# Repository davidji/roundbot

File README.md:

This is a 3D printable robot with MBED control software. It uses signal processing to reduce the component count normally associated with quadrature encoding.

There are also lots of other objects defined in [Solid Python](https://github.com/SolidCode/SolidPython) loosely associated with the project

The build and all the dependencies for the software come from [PlatformIO](http://platformio.org/).

The 3D models require [Solid Python](https://github.com/SolidCode/SolidPython) and [OpenSCAD](http://www.openscad.org/)

TODO: The hardware needs some explanation

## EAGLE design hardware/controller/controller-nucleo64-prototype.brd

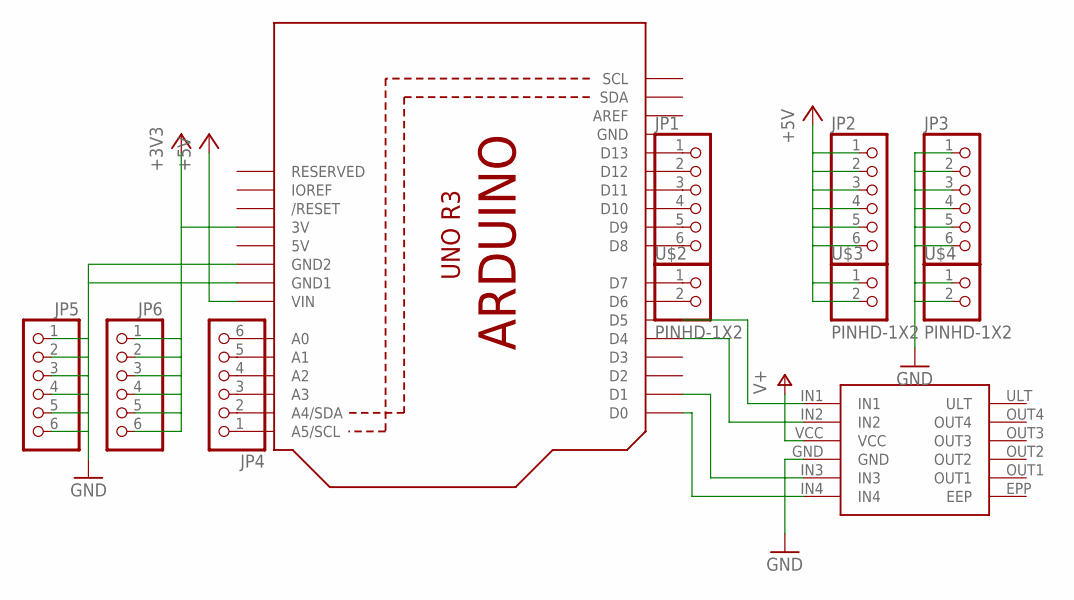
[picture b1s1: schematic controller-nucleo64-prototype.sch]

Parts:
JP1, JP2, JP3, JP4, JP5, JP6: PINHD-1X6CB; 1X06-CLEANBIG
U1: ARDUINOR3-DIMENSION; ARDUINOR3
U$1: DRV8833-MODULEUPSIDE-DOWN; DRV8833-BRKOUT-INV
U$2, U$3, U$4: PINHD-1X2; 1X02-CLEANBIG

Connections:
5V: U1.5V
+3V3: JP6.1, JP6.2, JP6.3, JP6.4, JP6.5, JP6.6, U1.3V
+5V: JP2.1, JP2.2, JP2.3, JP2.4, JP2.5, JP2.6, U1.VIN, U$3.1, U$3.2
GND: JP3.1, JP3.2, JP3.3, JP3.4, JP3.5, JP3.6, JP5.1, JP5.2, JP5.3, JP5.4, JP5.5, JP5.6, U1.GND, U1.GND1, U1.GND2, U$1.GND, U$4.1, U$4.2
unnamed: U1.D0, U$1.IN4
unnamed: U1.D1, U$1.IN3
unnamed: U1.D4, U$1.IN2
unnamed: U1.D5, U$1.IN1
unnamed: JP1.1, U1.D13
unnamed: JP1.2, U1.D12
unnamed: JP1.3, U1.D11
unnamed: JP1.4, U1.D10
unnamed: JP1.5, U1.D9
unnamed: JP1.6, U1.D8
unnamed: JP4.1, U1.A5 (A5/SCL)
unnamed: JP4.2, U1.A4 (A4/SDA)
unnamed: JP4.3, U1.A3
unnamed: JP4.4, U1.A2
unnamed: JP4.5, U1.A1
unnamed: JP4.6, U1.A0
unnamed: U1.D7, U$2.1
unnamed: U1.D6, U$2.2
V+: U$1.VCC

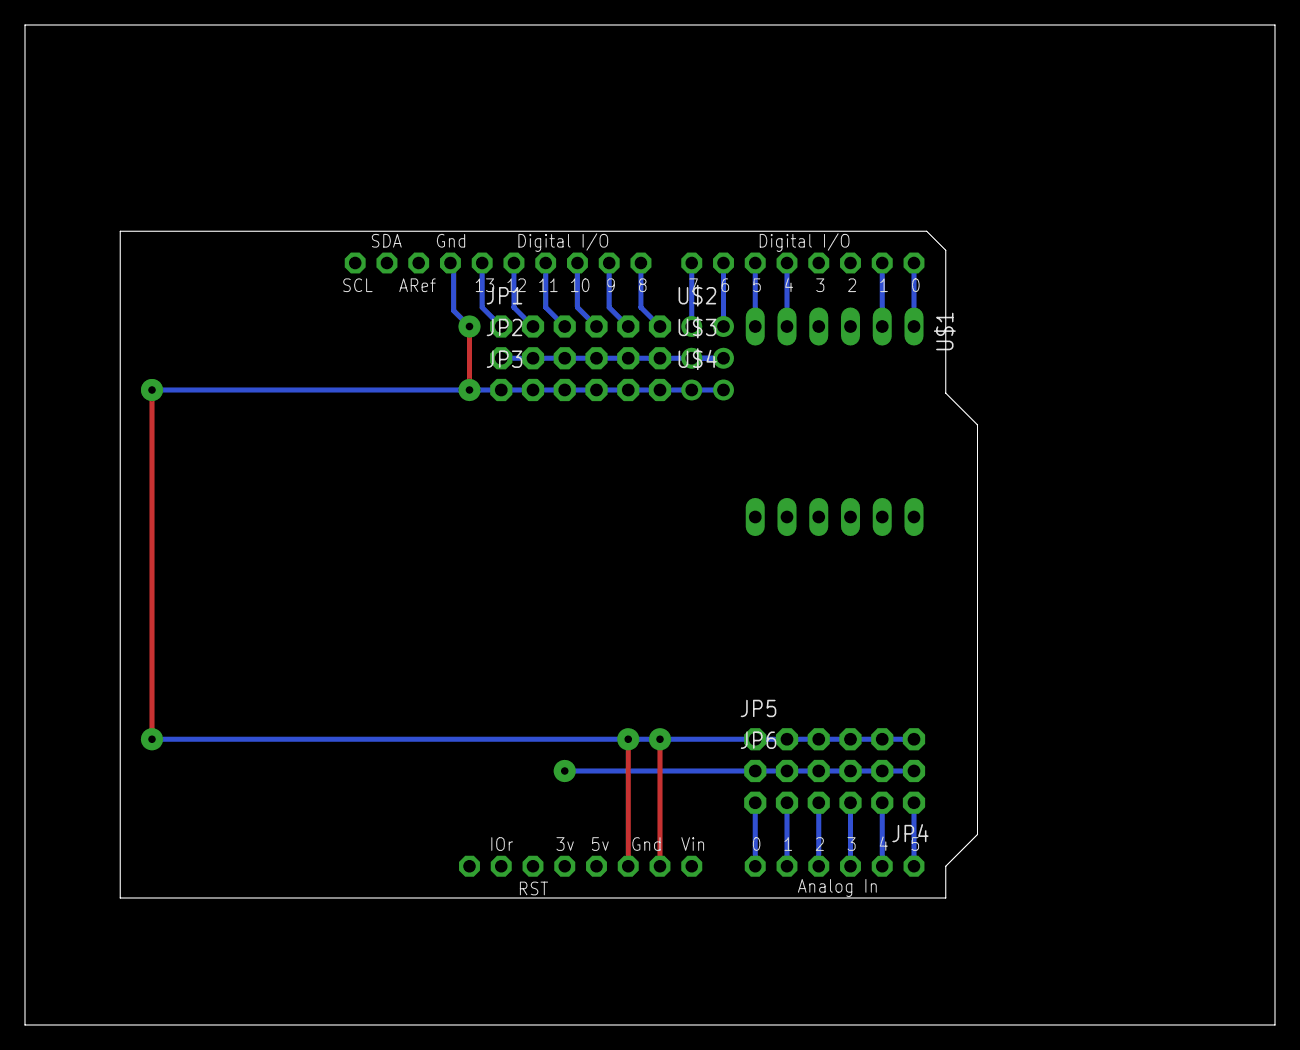
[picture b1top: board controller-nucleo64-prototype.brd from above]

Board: 2 copper layers, 100.0 x 80.0 mm, 11 parts (0 on the bottom side), 21 nets.

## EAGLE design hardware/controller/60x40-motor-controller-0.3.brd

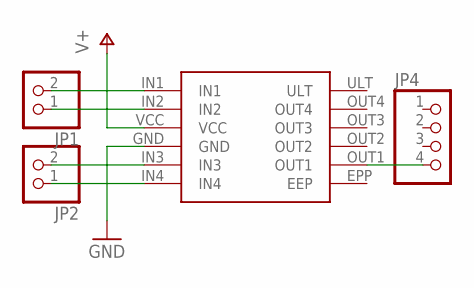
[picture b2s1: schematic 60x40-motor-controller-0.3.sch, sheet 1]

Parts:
JP1, JP2: PINHD-1X2/90; 1X02/90
JP4: PINHD-1X4/90; 1X04/90
U$1: DRV8833-MODULE; DRV8833-BRKOUT

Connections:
GND: U$1.GND; also elsewhere on the board
unnamed: JP2.2, U$1.IN3
unnamed: JP2.1, U$1.IN4
unnamed: JP1.2, U$1.IN1
unnamed: JP1.1, U$1.IN2
unnamed: JP4.4, U$1.OUT1
V+: U$1.VCC; also elsewhere on the board

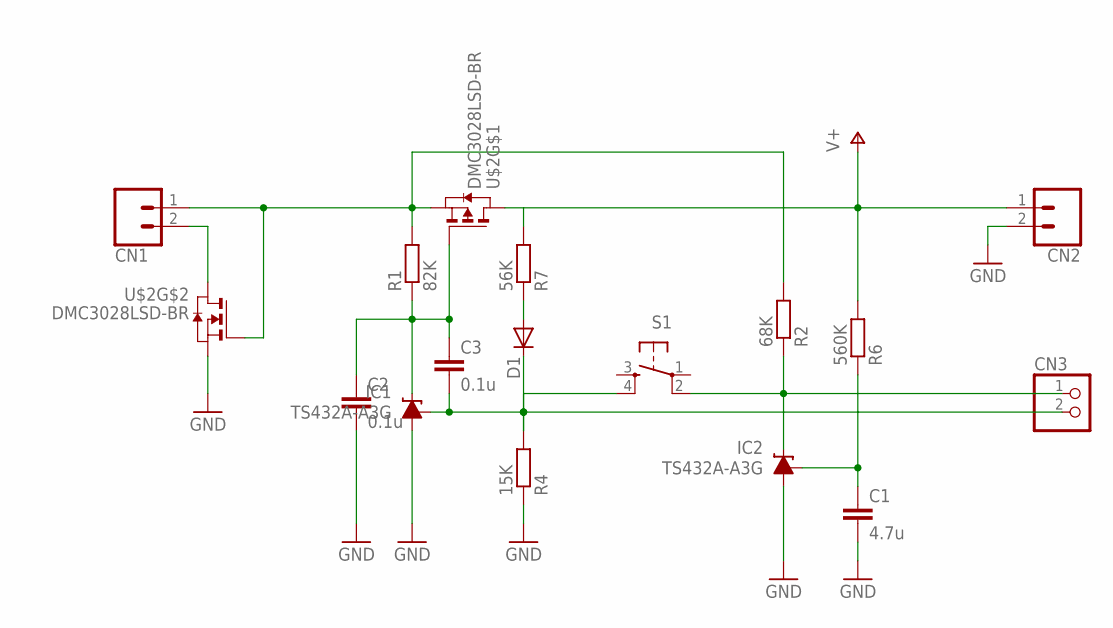
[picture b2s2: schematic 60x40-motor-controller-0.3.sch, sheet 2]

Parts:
C1: 4.7u; C025-025X050
C2, C3: 0.1u; C025-024X044
CN1, CN2: CONN_02-JST-XTH; JST-2-XTH
CN3: PINHD-1X2/90; 1X02/90
D1: DIODE-D-5; D-5
IC1, IC2: TS432A-A3G; TO92-LINE
R1: 82K; 0204V
R2: 68K; 0204/7
R4: 15K; 0204V
R6: 560K; 0207/10
R7: 56K; 0204V
S1: PROTO-MICRO-SWITCH; B3F-10XX-PROTO
U$2: DMC3028LSD-BR; DIL8-BREAKOUT

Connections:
GND: C1.2, C2.2, CN2.2, IC1.2 (A), IC2.2 (A), R4.1, U$2.1 (S); also elsewhere on the board
unnamed: CN1.1, R1.2, R2.2, U$2.2 (G), U$2.3 (S)
unnamed: C2.1, C3.1, IC1.1 (C), R1.1, U$2.4 (G)
unnamed: CN1.2, U$2.7 (D), U$2.8 (D)
unnamed: C3.2, CN3.2, D1.C, IC1.3 (FB), R4.2, S1.4 (S1)
unnamed: CN3.1, IC2.1 (C), R2.1, S1.2 (P1)
unnamed: C1.1, IC2.3 (FB), R6.1
unnamed: D1.A, R7.1
V+: CN2.1, R6.2, R7.2, U$2.5 (D), U$2.6 (D); also elsewhere on the board

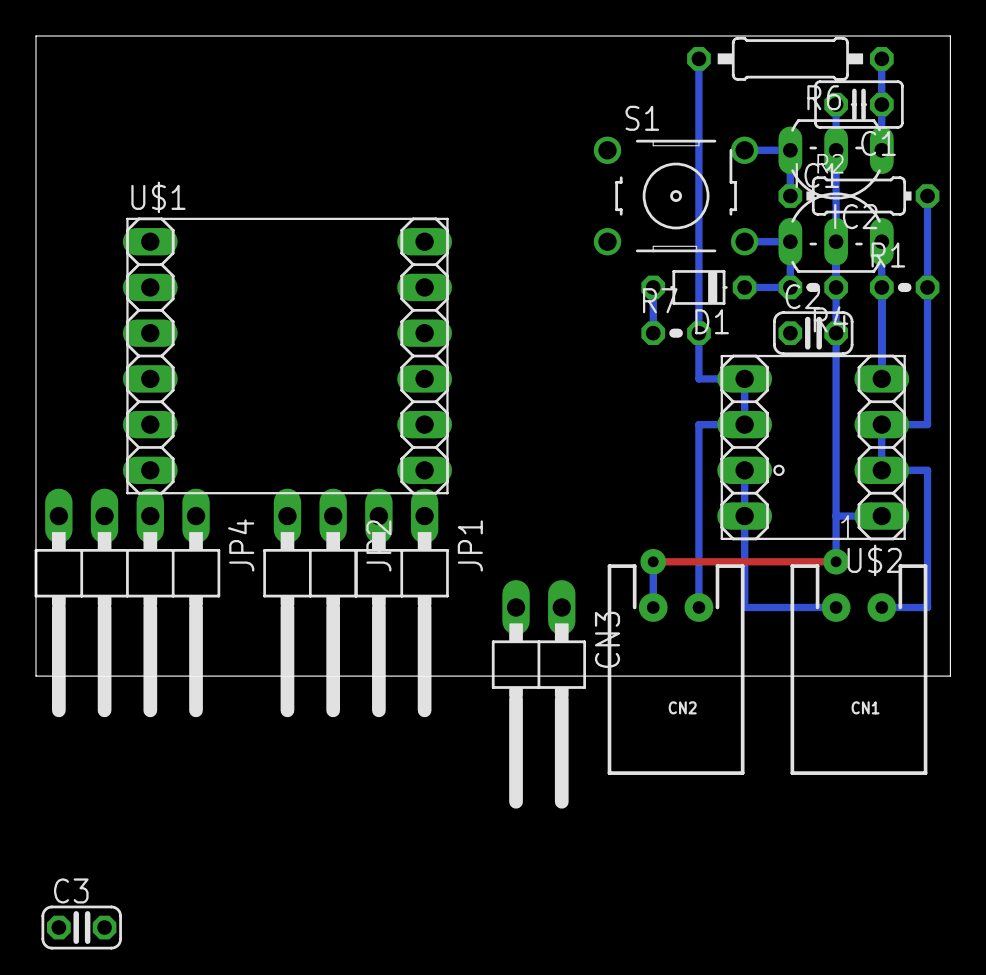
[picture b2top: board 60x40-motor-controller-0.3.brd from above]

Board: 2 copper layers, 50.8 x 35.6 mm, 20 parts (0 on the bottom side), 14 nets.

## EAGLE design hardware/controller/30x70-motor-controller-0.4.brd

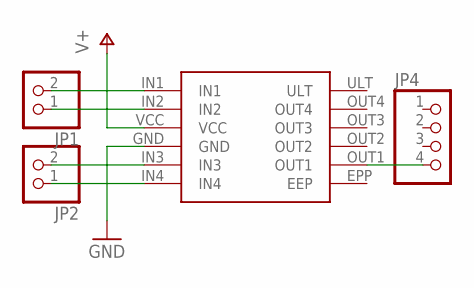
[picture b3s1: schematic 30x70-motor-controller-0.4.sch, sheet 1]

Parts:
JP1, JP2: PINHD-1X2/90; 1X02/90
JP4: PINHD-1X4/90; 1X04/90
U$1: DRV8833-MODULE; DRV8833-BRKOUT

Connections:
GND: U$1.GND; also elsewhere on the board
unnamed: JP2.2, U$1.IN3
unnamed: JP2.1, U$1.IN4
unnamed: JP1.2, U$1.IN1
unnamed: JP1.1, U$1.IN2
unnamed: JP4.4, U$1.OUT1
V+: U$1.VCC; also elsewhere on the board

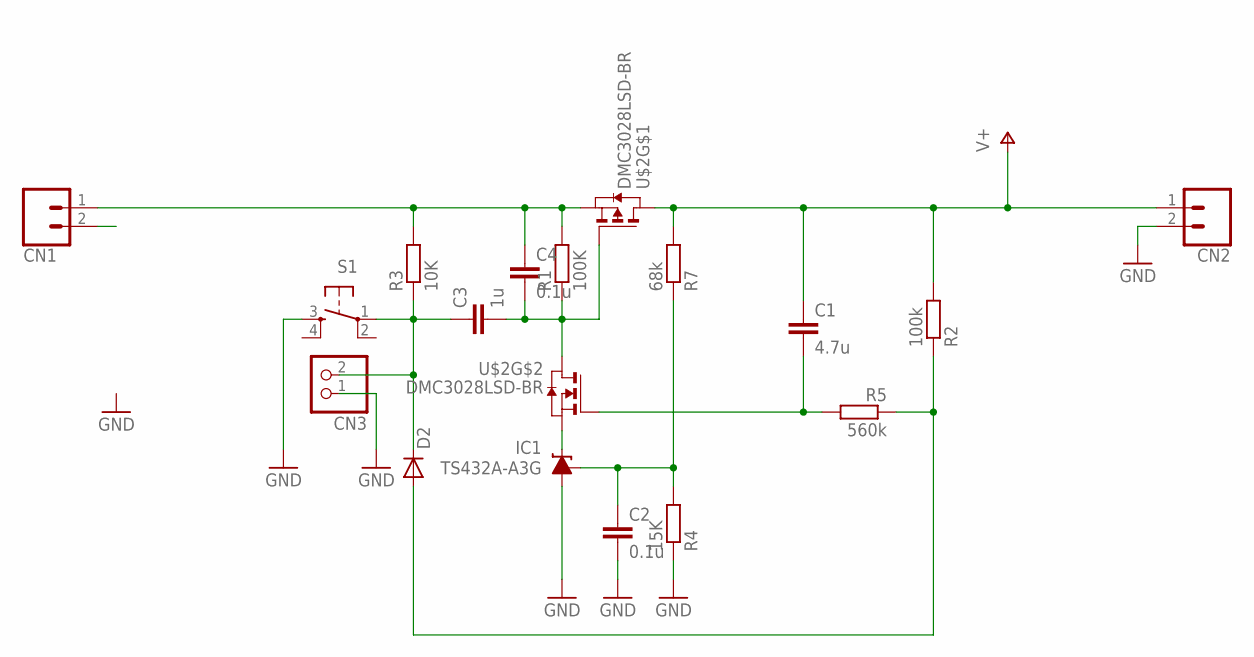
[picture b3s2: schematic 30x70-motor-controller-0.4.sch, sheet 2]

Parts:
C1: 4.7u; C025-025X050
C2, C4: 0.1u; C025-024X044
C3: 1u; C025-024X044
CN1, CN2: CONN_02-JST-XTH; JST-2-XTH
CN3: PINHD-1X2/90; 1X02/90
D2: DIODE-D-2.5; D-2.5
IC1: TS432A-A3G; TO92-LINE
R1: 100K; 0204V
R2: 100k; 0204V
R3: 10K; 0204V
R4: 15K; 0204V
R5: 560k; 0204/7
R7: 68k; 0204/7
S1: PROTO-MICRO-SWITCH; B3F-10XX-PROTO
U$2: DMC3028LSD-BR; DIL8-BREAKOUT

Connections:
GND: C2.2, CN2.2, CN3.1, IC1.2 (A), R4.1, S1.3 (S); also elsewhere on the board
unnamed: C4.1, CN1.1, R1.2, R3.2, U$2.3 (S)
unnamed: C3.2, C4.2, R1.1, U$2.4 (G), U$2.7 (D), U$2.8 (D)
unnamed: C2.1, IC1.3 (FB), R4.2, R7.1
unnamed: C1.2, R5.2, U$2.2 (G)
unnamed: D2.A, R2.1, R5.1
unnamed: IC1.1 (C), U$2.1 (S)
unnamed: C3.1, CN3.2, D2.C, R3.1, S1.1
V+: C1.1, CN2.1, R2.2, R7.2, U$2.5 (D), U$2.6 (D); also elsewhere on the board

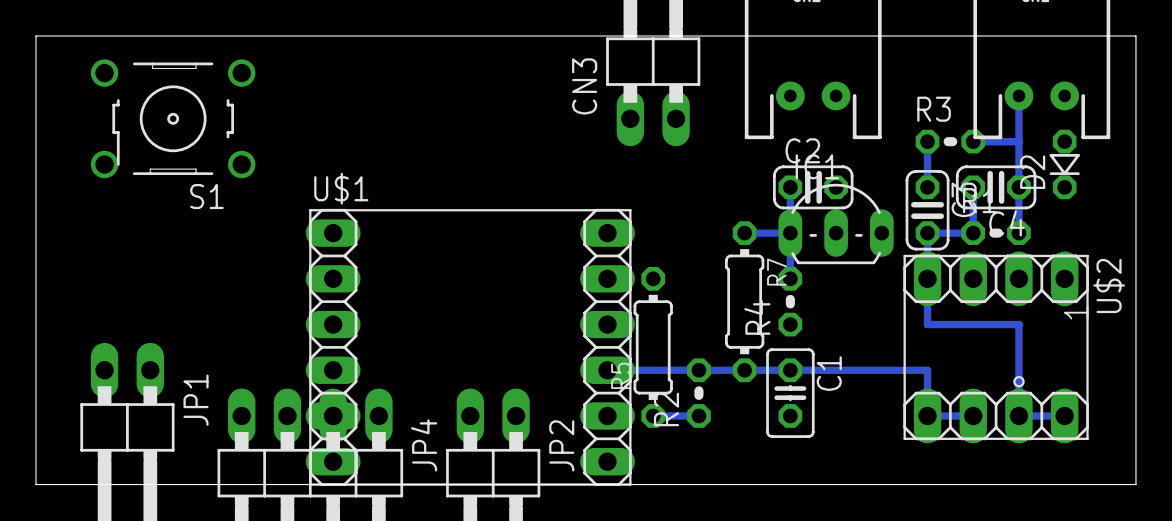
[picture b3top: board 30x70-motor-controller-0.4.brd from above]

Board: 2 copper layers, 61.1 x 24.9 mm, 21 parts (0 on the bottom side), 14 nets.

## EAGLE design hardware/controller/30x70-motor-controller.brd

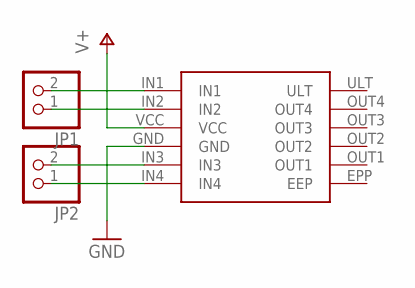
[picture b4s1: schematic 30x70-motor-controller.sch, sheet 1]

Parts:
JP1, JP2: PINHD-1X2/90; 1X02/90
U$1: DRV8833-MODULE; DRV8833-BRKOUT

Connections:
GND: U$1.GND; also elsewhere on the board
unnamed: JP2.2, U$1.IN3
unnamed: JP2.1, U$1.IN4
unnamed: JP1.2, U$1.IN1
unnamed: JP1.1, U$1.IN2
V+: U$1.VCC; also elsewhere on the board

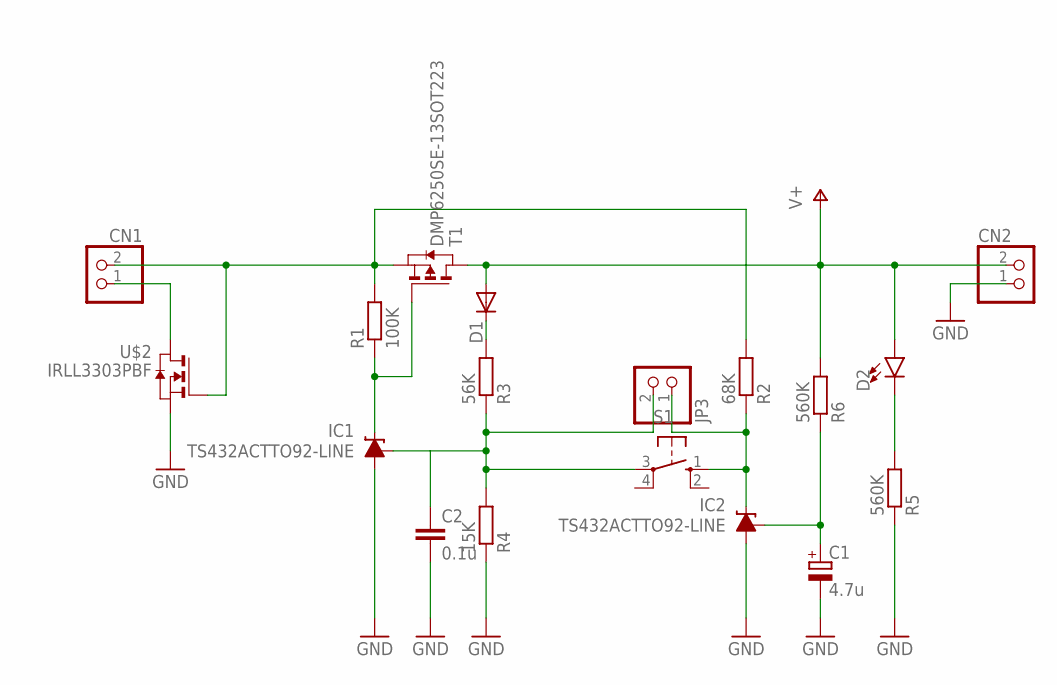
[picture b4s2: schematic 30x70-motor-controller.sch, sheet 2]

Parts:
C1: 4.7u; E2,5-5
C2: 0.1u; C025-024X044
CN1, CN2: JST_2PIN-THM-RA; JST-PH-2-THM-RA
D1: DIODE-D-2.5; D-2.5
D2: LED-3MM-NO_SILK; LED_3MM-NS
IC1, IC2: TS432ACTTO92-LINE; TO92-LINE
JP3: PINHD-1X2/90; 1X02/90
R1: 100K; 0204/5
R2: 68K; 0204/5
R3: 56K; 0204/5
R4: 15K; 0204V
R5, R6: 560K; 0204/5
S1: 10-XX; B3F-10XX
T1: DMP6250SE-13SOT223; SOT223
U$2: IRLL3303PBF; SOT223

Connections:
GND: C1.-, C2.2, CN2.1 (2), IC1.2 (A), IC2.2 (A), R4.1, R5.1, U$2.3 (S); also elsewhere on the board
unnamed: CN1.2 (1), R1.2, R2.2, T1.3 (S), U$2.1 (G)
unnamed: IC1.1 (C), R1.1, T1.1 (G)
unnamed: CN1.1 (2), U$2.2 (D), U$2.4 (D)
unnamed: C2.1, IC1.3 (FB), JP3.2, R3.1, R4.2, S1.3
unnamed: IC2.1 (C), JP3.1, R2.1, S1.1 (S)
unnamed: C1.+, IC2.3 (FB), R6.1
unnamed: D1.C, R3.2
unnamed: D2.K (C), R5.2
V+: CN2.2 (1), D1.A, D2.A, R6.2, T1.2 (D), T1.4 (D); also elsewhere on the board

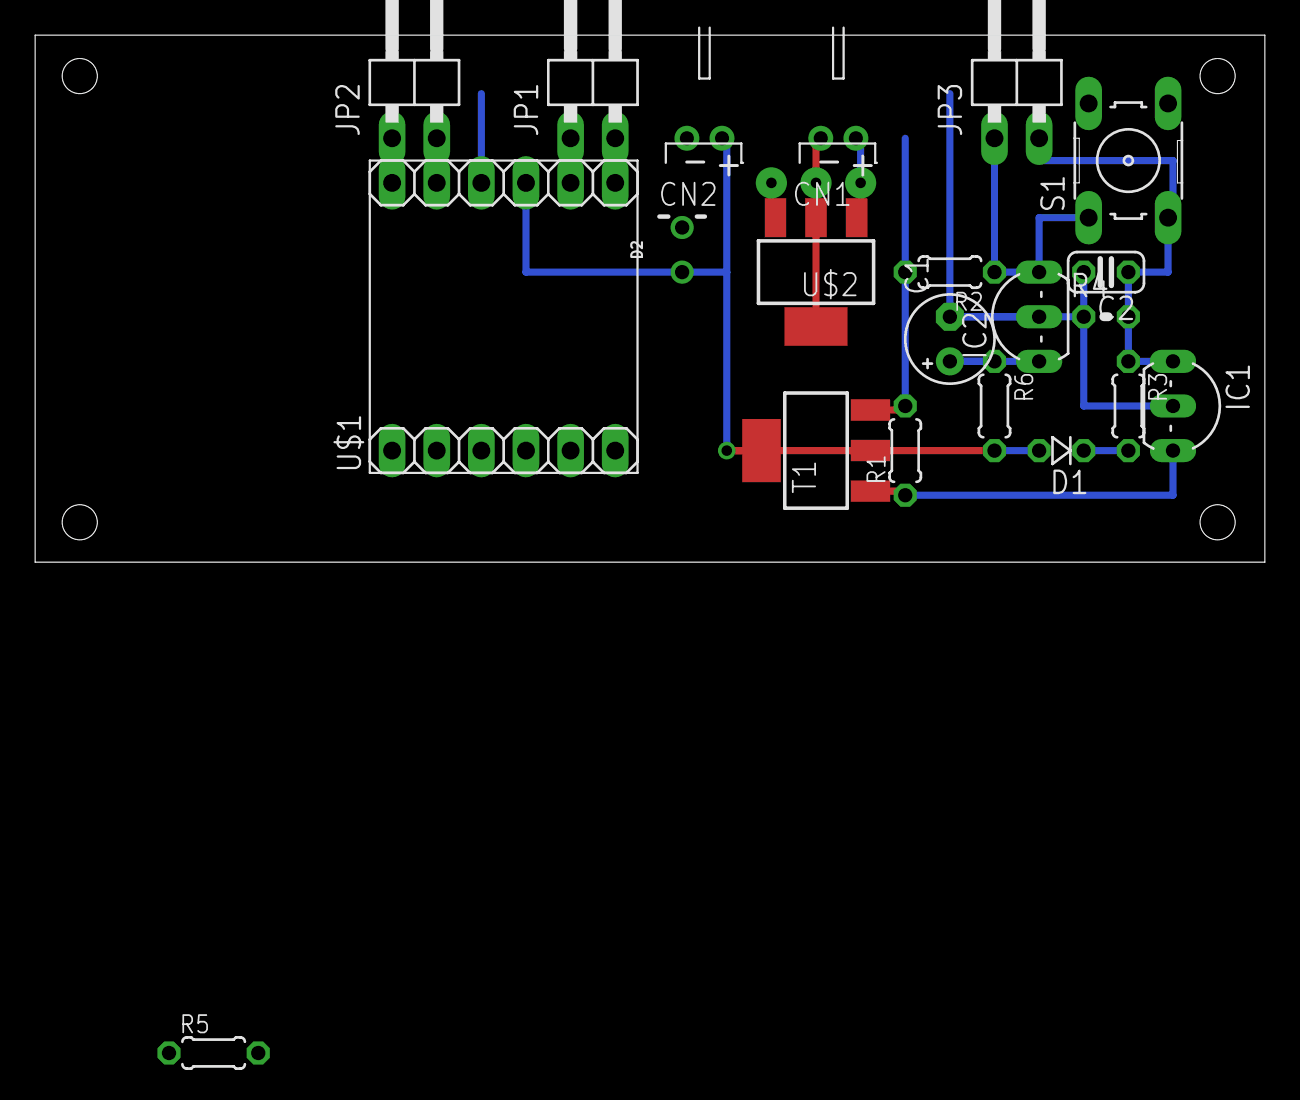
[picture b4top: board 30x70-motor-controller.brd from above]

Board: 2 copper layers, 70.0 x 30.0 mm, 21 parts (0 on the bottom side), 14 nets.

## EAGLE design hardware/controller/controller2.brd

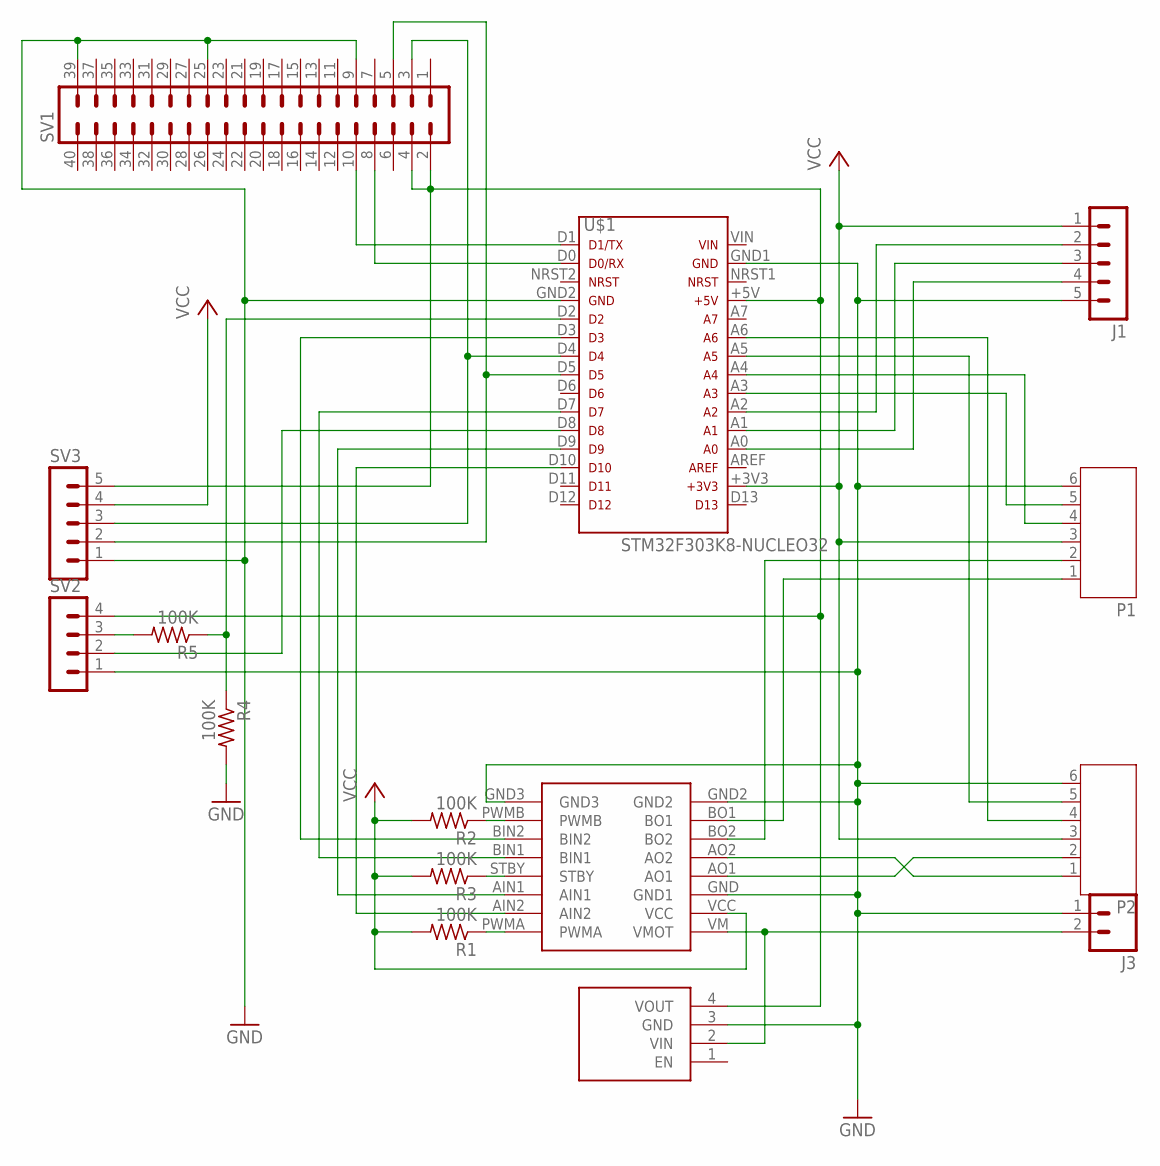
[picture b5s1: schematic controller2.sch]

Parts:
J1: MA05-1
J3: M02JST-PTH-VERT; JST-2-PTH-VERT
P1, P2: JST-PH6
R1, R2, R3, R4, R5: 100K; M0805
SV1: MA20-2
SV2: MA04-1
SV3: MA05-1
U$1: STM32F303K8-NUCLEO32; NUCLEO32
U$2: TB6612FNG-CARRIER/SPARKFUN; TB6612FNG-BRKOUT/SPARKFUN
U$3: S7V8A; S7V8

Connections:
GND: J1.5, J3.1, P1.6, P2.6, R4.2, SV1.9, SV1.25, SV1.39, SV2.1, SV3.1, U$1.GND1, U$1.GND2, U$2.GND (GND1), U$2.GND2, U$2.GND3, U$3.3 (GND)
unnamed: U$1.D3, U$2.BIN2
unnamed: U$1.D7, U$2.BIN1
unnamed: U$1.D9, U$2.AIN1
unnamed: U$1.D10, U$2.AIN2
unnamed: P2.2, U$2.AO1
unnamed: R2.1, U$2.PWMB
unnamed: R1.1, U$2.PWMA
unnamed: R3.1, U$2.STBY
unnamed: P2.1, U$2.AO2
unnamed: P1.2, U$2.BO2
unnamed: P1.1, U$2.BO1
unnamed: SV1.3, SV3.3, U$1.D4
unnamed: SV1.5, SV3.2, U$1.D5
unnamed: SV1.8, U$1.D0
unnamed: SV1.10, U$1.D1
unnamed: J3.2, U$2.VM (VMOT), U$3.2 (VIN)
unnamed: P1.4, U$1.A4
unnamed: P1.5, U$1.A3
unnamed: P2.4, U$1.A6
unnamed: P2.5, U$1.A5
unnamed: J1.2, U$1.A2
unnamed: J1.3, U$1.A1
unnamed: J1.4, U$1.A0
unnamed: R5.2, SV2.3
unnamed: SV1.2, SV1.4, SV2.4, SV3.5, U$1.+5V, U$3.4 (VOUT)
unnamed: R4.1, R5.1, U$1.D2
unnamed: SV2.2, U$1.D8
VCC: J1.1, P1.3, P2.3, R1.2, R2.2, R3.2, SV3.4, U$1.+3V3, U$2.VCC

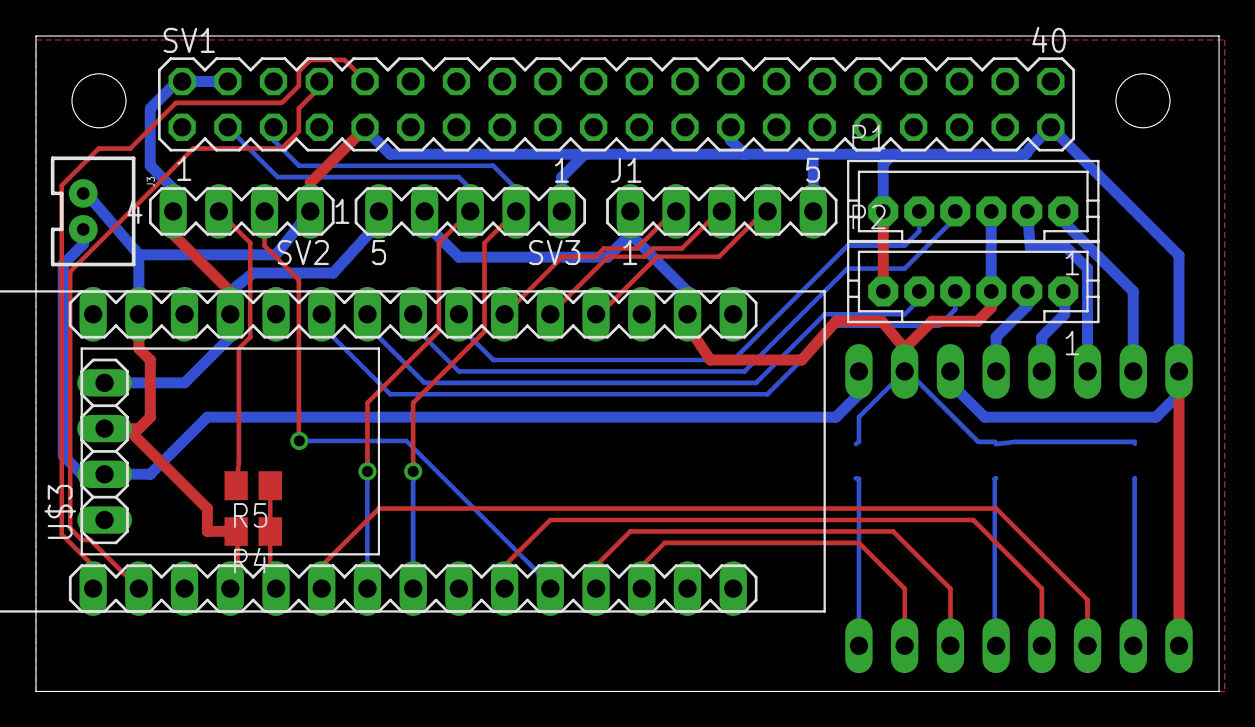
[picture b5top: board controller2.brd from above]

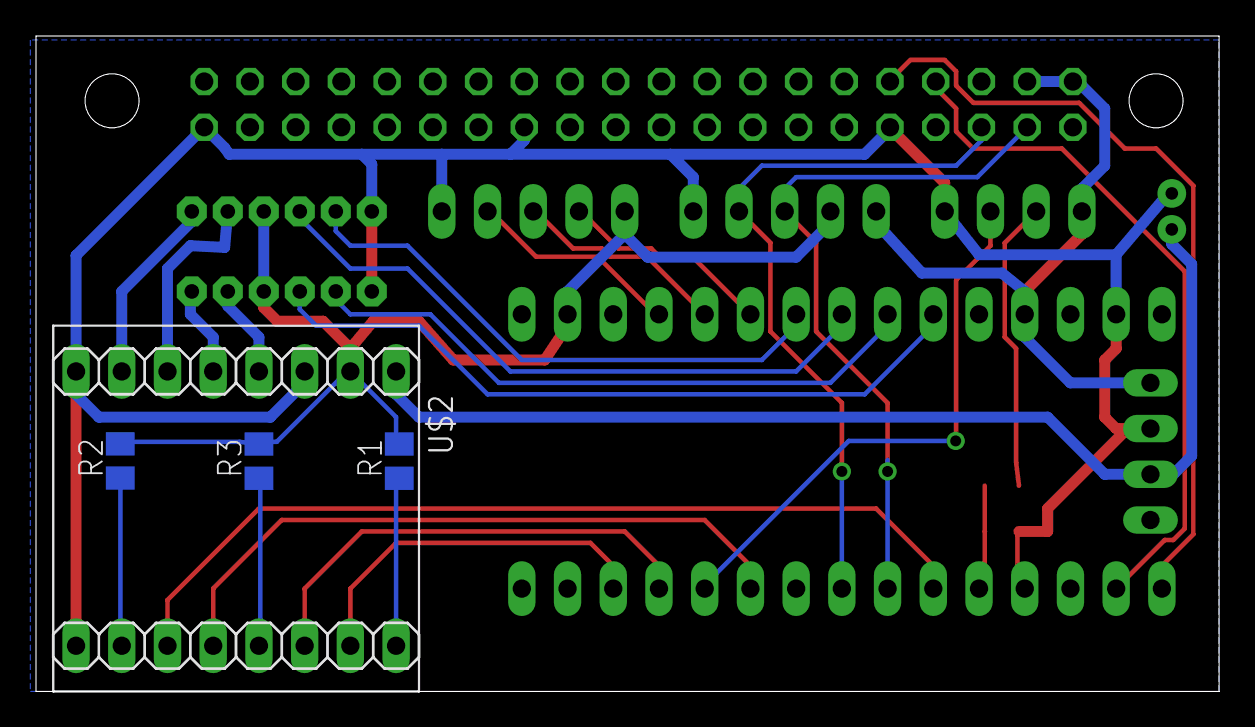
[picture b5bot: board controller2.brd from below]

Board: 2 copper layers, 65.7 x 36.4 mm, 15 parts (4 on the bottom side), 29 nets.

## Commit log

2016-04-06 initial version
2016-04-16 3 caster design leaving room for line following sensors at the front
2016-04-17 added drawing of caster mounts
2016-05-02 hardware notes
2016-05-02 table formatting
2016-05-02 table formatting again
2016-05-10 alternate 3d chassis, new flat chassis
2016-05-10 source project
2016-05-11 Reasonably complete laser cut version
2016-06-07 stuff
2016-06-11 this seems to have captured my hosts path. sigh. Anyway, some notes on rotary encoding
2016-06-11 change wiring so nucleo serial port works
2016-06-11 add motor encoder support
2016-06-13 None of this works. about to switch to chibios
2016-06-13 C++ 11
2016-06-17 It's important not to attach a function to the ticker before main() starts - it will just get disconnected
2016-06-18 track min and max for both channels, have separate zeros. This actually seems to be working now
2016-06-19 Get rid of the enable pins - they will just be pull up resistors. Fix a bug in break mode. Improvements in logging
2016-07-03 add eagle cad files for controller
2016-07-30 gerber
2016-08-19 auto ranging for rotary encoder, a few changes to the chassis, add rangefinder test
2016-08-19 bulkhead for range finder
2016-08-21 some corrections to the lid, ready for a new print, added a bit of lego support, finished off bulkhead for printing
2016-08-31 This sort of works, in that it knows roughly when it's turned 1/4. It doesn't work, in that it makes no sense to use a pid controller this way.
2016-09-15 shell for control via serial port
2016-09-22 RaspberryPi has M2.5 holes, add nucleo 64 mount points
2016-09-22 Compensate for friction, I think
2016-10-08 updates for new mbed
2016-10-08 a python client
2016-12-04 Chassis changes for PETG + integral battery, motor mounts
2016-12-04 honeycomb base to reduce build plate adhesion, which is a problem for PETG
2016-12-08 LICENSE created online with Bitbucket
2016-12-24 Update for Nucleo STM21F303RE
2016-12-24 Add time of flight, changes for platformio 3, switch to Nucleo F303RE
2017-01-27 Assorted 3d printed parts, switch to nucleo64 board
2017-02-11 Box for the nucleo-64 st-link board.
2017-02-21 More hardware stuff
2017-02-21 README.md edited online with Bitbucket
2017-05-28 Improvements to chassis: motor mount resists twisting better, cover for batteries to hold them in, flat top for easier composing of modules
2017-05-28 work in progress: head segment
2017-05-29 Support combining body 'modules' into a complete ring. More work on the eyes 'module'
2017-06-01 A cage for module pcbs. A couple of different configurations, neither finalised
2017-06-05 refectoring into classes for more composition
2017-06-16 A cover for a wifi piggy backed on a raspberry pi zero, using a split pin holder for the module
2017-06-16 A few feather wing related things
2017-06-16 A panel mount for a sub-miniture joystick
2017-06-16 various messing around with mounting the electronics in the chassis
2017-06-16 Add support for a different micro-controller
2017-07-05 Just lots of stuff...
2017-07-26 holder for modules with headers
2017-07-26 new layering of chassis to avoid lots of support material
2017-07-26 changes for new version of mbed
2017-07-29 add subrepo
2017-07-29 fix some bitrot: moveing to MBED 5?
2017-07-30 This builds without RTOS. Building with RTOS doesn't work
2017-08-03 something to attach all the electronics too, which is fairly agile
2017-10-26 mostly soft switch related stuff
2017-10-26 model for a barrel dc connector I have a few of
2017-11-04 motor controller board
2017-11-04 An alternative handle for adafruits curcuit playground wand
2017-11-18 Lots of controller designs
2017-11-18 Various messing around trying to get mbed to do ADC fast enough

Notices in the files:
parts and their libraries:
SparkFun-LED: Licensing: Creative Commons ShareAlike 4.0 International - https://creativecommons.org/licenses/by-sa/4.0
